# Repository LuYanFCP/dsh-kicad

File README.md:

# dsh-kicad

English | [中文](README.zh.md)

KiCad for [DeepSeek Harness](https://github.com/deepseek-ai/deepseek-harness) (dsh): a native dsh plugin bundle that lets the agent read, edit and check KiCad schematics, with KiCad itself (`kicad-cli`) deciding whether the design is correct.

> Developer preview. Built and tested against dsh `0.2.1-rc.2` and KiCad `10.0.7`. dsh's plugin APIs are pre-stable, so every package pins `engines.dsh` to `>=0.2.1-rc.2 <0.3.0-0`.

## What you get

| Surface | What it does |
|---|---|
| **Tools** (`kicad_*`) | `doctor` (is this machine ready: kicad-cli and KiCad 8+, libraries, Python, with fixes and install commands), `read_schematic`, `list_components`, `get_symbol_pins`, `list_nets` (KiCad netlist), `search_symbols` (installed libraries), `erc`, `drc`, `render` (SVG, PNG attached as an image for image-capable models; for boards KiCad's 3D view from any side or angle), `export` (netlist/BOM), `simulate` (SPICE verification with ngspice: operating point, transient and AC runs, with requirement assertions judged on the numbers, see [Simulation](#simulation)), `sim_model` (find the SPICE models in a model file or folder, with their pins), `check_mcu` (static check of how a microcontroller is wired, see [MCU wiring check](#mcu-wiring-check)), `datasheet` (read a part's datasheet PDF: its sections, search, whole pages) and `check_design` (unit tests for the schematic, quoted from the datasheets; see [Datasheet checks](#datasheet-checks)), `simulate_firmware` (run an ATtiny or ESP32 firmware against the board, see [Firmware against the board](#firmware-against-the-board)), `export_fab` (Gerber/drill/position/BOM zip with 3D previews, refused until KiCad finds the board ready, see [Fab output](#fab-output)), `fab_preset` (JLCPCB/PCBWay design rules), `create_schematic`, and `edit_schematic` — an atomic batch of edits (add/move/remove symbols, set values/footprints/properties, wires, labels, power symbols, junctions, no-connects, pin-to-pin wires routed around parts and other nets, pin-to-net connections, plus layout by function: titled block frames, moving a part or a whole block together with its wiring, page size and title block); for boards `read_pcb` (outline, layers, rules and net classes, footprints with courtyards and pad nets, zones, DRC's unrouted count) and `edit_pcb` — an atomic batch (board outline and mounting holes, moving, flipping and locking footprints, design rules and net classes in the `.kicad_pro`, tracks with pad-to-pad endpoints, vias, zones, keepouts, silkscreen text and reference designators, removal by uuid); and `update_pcb` — Update PCB from Schematic, headless: a new board gets KiCad's empty board, a default stackup and a placeholder outline; on an existing board placed footprints stay put, new ones are staged beside the outline, and nets, values and fields follow the schematic; it refuses with the `REF:PIN`s to fix, and KiCad's schematic parity check judges the result; and `autoroute` — routes the board with [Freerouting](https://github.com/freerouting/freerouting), keeping hand-routed (locked) and existing tracks, refilling copper pours, with KiCad's DRC as the verdict (see [Routing](#routing)). Untouched file text stays byte-identical. |
| **Policy** | Design edits go through dsh approval (`ask`); writes are confined to the session's working directory (a monotonic guard); after every successful edit KiCad ERC (schematic) or DRC (board edit or fab preset, zones refilled; with the schematic parity count after `update_pcb`) runs and its verdict is appended to the tool result, and so are the project's design checks that fail after a schematic edit; the system prompt gets stable KiCad working rules and a dynamic "KiCad project in this directory + last ERC/DRC" context. |
| **Skills** | `kicad-agent-workflow`, `kicad-design-brief`, `kicad-erc-triage`, `kicad-drc-triage`, `kicad-schematic-design`, `kicad-datasheet-checks` (read each part's datasheet and keep its requirements as checks), `kicad-pcb-layout` (from the synced schematic to the fab files: rules, placement, critical nets, GND pour, autoroute, DRC, fab output, each step judged by KiCad), `kicad-simulate`, `kicad-mcu-check`. |
| **Commands** | `/erc`, `/drc`, `/bom`, `/simulate`, `/design-checks`, `/mcu-check` and `/mcu-sim` (model-free, run on the project's root design), `/kicad-fab` (fab zip), `/kicad-render`, `/kicad-doctor` (environment check), `/kicad-install` (install KiCad, the Freerouting autorouter or Espressif's QEMU for ESP32 firmware simulation, see below). |
| **Agent preset** | `eda` — a standard-like tool set with an electronics-design persona. The KiCad tools are global, so every preset can use them. |
| **Web UI** | Right-sidebar viewer for `*.kicad_sch` / `*.kicad_pcb` with two modes: **Interactive** — the embedded [KiCanvas](https://github.com/theacodes/kicanvas) viewer (hierarchical sheets, symbol/footprint/net inspection, layer toggles, KiCad or Witch Hazel theme, reloads when the file changes) — and **SVG** (kicad-cli render, pan/zoom, multi-sheet, Render button, re-renders a board by itself when it changes; also the automatic fallback); boards also get **3D**, modelled on KiCad's 3D Viewer (see [3D view](#3d-view)); conversation cards for ERC/DRC, schematic and board edits (with the automatic ERC/DRC verdict), Update PCB (the changes, the parts waiting for placement, KiCad's parity count), autoroute (what Freerouting added, KiCad's unrouted count and DRC errors), fab output (the gate, the files, **Download zip**, the 3D preview) and the environment check; with **Follow agent** on, a board opens in the sidebar while the agent syncs, edits or routes it, as a schematic does; settings pages for the sidecar (the kicad-cli, Python, Java, Freerouting, ngspice and QEMU paths, plus the KiCad environment check and **Install KiCad**) and the policy (approval, auto-ERC, auto-DRC, auto-render). The viewer and failed tool cards show a notice with **Install KiCad** when KiCad is missing or too old. |
| **Standalone MCP server** | The Python sidecar speaks MCP over stdio, so Claude Code or an RL environment can use the same tools without dsh. |
| **KiCad side (optional)** | An IPC plugin with an "Open in DSH" toolbar action. |

## Architecture

```
dsh-kicad-bundle  (cordis.patch.yml: global rows + presets/eda.patch.yml)
├─ dsh-kicad-bridge     Host  ctx.kicad service; runs the Python sidecar through ctx.subprocess, speaks MCP to it
│    └─ sidecar/        Python ≥3.10, stdlib-only core: lossless .kicad_sch S-expression editing, symbol libraries,
│                       pin geometry, kicad-cli (ERC/DRC/netlist/BOM/SVG), fab output; optional extras: png (cairosvg), ipc (kicad-python)
├─ dsh-tool-kicad       Host  kicad_* tools (defineTool), paths resolved against the session working directory
├─ dsh-kicad-policy     Host  tools.guard + tools/pre-execute (ask/deny) + tools/post-execute (auto ERC/DRC) + prompt section/context
├─ dsh-kicad-skills     Host  skill provider + /erc /drc /bom /kicad-fab /kicad-render
└─ dsh-client-ui-kicad  Client sidebarRightTabs type + tool.call.toolview rows + plugins.row.config pages
kicad-plugin/           KiCad IPC plugin ("Open in DSH")
market/                 plugin-market index example
```

Design decisions:

- **Files first, headless.** Schematics are edited as files (`.kicad_sch` S-expressions) and judged with `kicad-cli`; no KiCad GUI is needed. The IPC API (`kipy`) is only an optional live channel (`ipc_status`), because it needs a running GUI and admits one client at a time.
- **Python sidecar**, not Node → IPC: KiCad's IPC is NNG + protobuf with an official binding only for Python.
- **KiCad decides.** ERC/DRC verdicts come from `kicad-cli`, never from the model.
- **Narrow dsh coupling.** Each package touches dsh only through one adapter module (`src/dsh.ts`, `src/client/dsh.ts`); the Client uses public seams only (`sidebarRightTabs`, keyed slots, `remote.workspaceFiles`, `remote.commands`, config forms) and imports no dsh Client package, as dsh asks of third-party UI plugins.

## Requirements

- dsh `>=0.2.1-rc.2 <0.3` (`npm i -g @deepseek-ai/dsh`), Node `>=22.19`, pnpm 11 (for building from source)
- Python `>=3.10` on `PATH` (`python3`; `python` on Windows) — no Python packages needed for the core
- KiCad 8+ with `kicad-cli` (tested with 10.0.7). Found via the setting, `$KICAD_CLI`, `PATH`, macOS/Windows install dirs, or Flatpak `org.kicad.KiCad`
- Optional: `rsvg-convert`, ImageMagick or the `png` extra for PNG renders; the `ipc` extra for the IPC channel; [ngspice](https://ngspice.sourceforge.io/) (`ngspice` on `PATH`, or `$NGSPICE`) for `kicad_simulate`; `pdftotext` from poppler (`poppler-utils`; or `$PDFTOTEXT`) for `kicad_datasheet`

### Check your setup and install KiCad

**Plugins → KiCad → KiCad bridge** shows the environment check: each item (kicad-cli, KiCad version ≥ 8, symbol and footprint libraries, Python ≥ 3.10, optional KiCad 3D models, PNG rasterizer and kicad-python) with its status and how to fix it. `/kicad-doctor` prints the same in a conversation, and the model has `kicad_doctor`; a tool that fails because KiCad is missing names the install command.

When KiCad is missing or too old, the page (and the viewer's notice) lists the ways to install it on this machine:

| Platform | Option | Runs from dsh? |
|---|---|---|
| Fedora | `sudo dnf install -y kicad` | no: needs root, shown with **Copy command** |
| Ubuntu and derivatives | KiCad PPA: `sudo add-apt-repository -y ppa:kicad/kicad-10.0-releases && sudo apt-get update && sudo apt-get install -y kicad` | no (root) |
| Debian | `sudo apt-get install -y kicad` | no (root) |
| Arch | `sudo pacman -S --needed kicad kicad-library` | no (root) |
| openSUSE | `sudo zypper install kicad` | no (root) |
| any Linux with flatpak | `flatpak remote-add --user … flathub` + `flatpak install --user flathub org.kicad.KiCad` | yes, per user, no root (about 1.5 GB) |
| macOS | `brew install --cask kicad` | yes, if Homebrew is installed |
| Windows | `winget install --id KiCad.KiCad -e` | yes, if winget is available (Windows may ask for permission) |
| everywhere | installer from kicad.org | link |

Nothing runs until you click **Install…** and confirm the exact command. dsh never runs `sudo`: root-only options are shown for you to run in a terminal, then **Check again**. A running install shows its log and can be stopped; when it finishes the bridge restarts its sidecar and checks again, so the new kicad-cli (including the Flatpak one, via `flatpak run --command=kicad-cli org.kicad.KiCad`) is used without restarting dsh. From a conversation: `/kicad-install` lists the options, `/kicad-install flatpak --yes` runs one, `/kicad-install status` follows it.

The settings page has no session of its own: it runs these checks through your most recent session, so open or start one first.

## Install

### From source (works today)

```sh
git clone https://github.com/LuYanFCP/dsh-kicad && cd dsh-kicad
pnpm install && pnpm run build
dsh plugin --profile web add "$PWD/packages/kicad-bundle"
dsh web
```

`dsh plugin … add <dir>` links the directory; leaf packages resolve through this checkout's `node_modules`, and dsh maps `@deepseek-ai/*` imports to the running installation. Rebuild and restart dsh after code changes. In the Web UI you can also use **Plugins → Install** with the same absolute path.

### Paste the repository URL (simplest)

In dsh, **Plugins → Add plugin**, enter `https://github.com/LuYanFCP/dsh-kicad` and install (or `dsh plugin --profile web add https://github.com/LuYanFCP/dsh-kicad`). The repository root is itself the `dsh-kicad` bundle; it loads the prebuilt `dist/dsh-kicad`. Append `#<tag-or-commit>` to pin a version.

### From the plugin market (search inside dsh)

dsh finds plugins through **plugin markets**: JSON indexes you add once. This repository publishes one.

1. **Plugins → Experimental plugins → More → Custom plugin markets**: switch it on. A **Discover** tab appears.
2. **Discover → Add index source**: `https://raw.githubusercontent.com/LuYanFCP/dsh-kicad/main/market/index.json`
3. Search, e.g. `kicad`, `原理图`, `电路板`, `circuit board`, then **Install → Enable now**. No restart needed.

The market entry installs `dist/dsh-kicad`, a single self-contained package built by `pnpm run dist` (`scripts/pack-dist.mjs`), from a pinned Git commit. The same package installs directly:

```sh
dsh plugin --profile web add "git+https://github.com/LuYanFCP/dsh-kicad.git#<commit>&path:/dist/dsh-kicad"
```

To publish a new version: `pnpm run dist`, commit, then add a version to `market/index.json` with that commit and check it with `node market/validate.mjs <dsh>/node_modules/@deepseek-ai/dsh-plugin-market-index`.

## Use

1. Open a session whose workspace contains a KiCad project (sidebar **Add workspace**). Optionally pick the **EDA agent** preset.
2. Ask, e.g. *"Add a 100 nF decoupling capacitor between +3V3 and GND next to U1 and make ERC pass."* The agent reads the design, sends one `kicad_edit_schematic` batch (you approve it), and reads the ERC verdict that the policy appends.
3. Open the `.kicad_sch` from **Workspace files**: the KiCad tab shows the render, refreshed after each agent edit; **Render** re-renders on demand.
4. `/erc`, `/drc`, `/bom` work without the model.
5. **Plugins → KiCad → KiCad bridge / KiCad policy** hold the settings.

### Schematics by functional block

A new design is drawn block by block, like a reference design. The agent first plans the blocks (title, parts, area on the page). It then builds one block per `kicad_edit_schematic` call and frames it with `add_block`: a dashed frame titled with the block's job and main part (`3V3 LDO — AMS1117-3.3`, `MCU — ATtiny85`), with short notes inside where a choice needs explaining. Blocks connect only through net labels and power symbols. After every batch that places or moves parts, the edit result names the parts outside every block, and the agent is not done while there are any. `kicad_read_schematic` lists the same parts as `outside_blocks`. An existing schematic keeps its organisation unless you ask to reorganise it. The board placement below follows the same blocks.

### Datasheet checks

A part's limits and the parts it needs come from its datasheet, not from the model's memory. `kicad_datasheet {path, reference | lib_id | url | pdf, query?, pages?}` reads the datasheet: the symbol's own link, a URL the agent found with `web_search`, or a PDF in the workspace. It downloads the PDF once into `.dsh-kicad/datasheets/`, extracts the text per page with `pdftotext`, and returns the pages of the usual sections (absolute maximum ratings, operating conditions, electrical characteristics, application information, layout), the lines matching a query, or whole pages. A link that leads to a web page or a zip is refused with what to do instead.

`kicad_check_design` turns those pages into unit tests for the schematic. Each check states one requirement and quotes the words it comes from. The checks are kept in `design-checks.json` next to the schematic, and the tool judges them on KiCad's netlist and the part values. Rules:

- `max_voltage`, `voltage_range`;
- `voltage_difference` (a regulator's dropout headroom);
- `capacitance` (every capacitor between two nets);
- `resistance` (pull-ups, pull-downs, series resistors);
- `same_net`;
- `led_current` (rail voltages, Vf and the series resistor).

A check counts only when its source holds: the quote must be in the datasheet text (or in a workspace file such as `design-brief.md`, for the user's own numbers), and it must state the check's numbers. Otherwise the check is CANNOT VERIFY, never passed. After every schematic edit the checks re-run and the failing ones are appended to the result; `/design-checks` runs them without the model.

On the AMS1117-3.3 the datasheet says "The addition of 22µF solid tantalum on the output will ensure stability for all operating conditions". A design with the usual 10 µF fails that check (`capacitance +3V3 → GND = 10.1 µF < 22 µF`); with 22 µF it passes. The `kicad-datasheet-checks` skill says what to take from each kind of part.

### Board placement

After `kicad_update_pcb` creates a board, one `kicad_edit_pcb` operation, `auto_place`, lays it out from the schematic's functional blocks (the `add_block` frames; without them its sheets, else net connectivity): each block stays together, connectors sit on the board edge facing out (a footprint's "PCB Edge" mark lands on the edge), decoupling capacitors go next to their IC's power pins and crystals next to their IC, power parts get extra room, and the outline is sized to fit (a drawn outline is kept and filled instead). `place_block` lays out one block in a given spot or rectangle. `kicad_read_pcb` then reports courtyard overlaps, footprints outside the outline and the total ratsnest length, and `kicad_render` with `view: "3d"` shows the result. On the usb-attiny85 board it gives no courtyard overlap, everything inside the outline, the USB-C on the edge, and a ratsnest of 214 mm against 345 mm for random placement ([details](docs/pcb-architecture.md#placement-12)).

### Routing

`kicad_autoroute {pcb, nets?, exclude_nets?, passes?, timeout?}` writes the board as a Specctra design, runs Freerouting headless, and adds only the new tracks and vias; footprints never move. Every track and via already on the board is fixed wiring, so the agent routes critical nets by hand first (power, USB or differential pairs, a crystal: `kicad_edit_pcb` `add_track` / `add_via` with `locked: true`) and the router completes the rest. Copper zones (a GND pour on both layers) are refilled and saved afterwards by `kicad-cli pcb drc --refill-zones --save-board`, whose verdict (unrouted count, DRC errors, schematic parity) is the result. The run can be cancelled from dsh and stops at `timeout` (default 300 s), keeping what it routed; the design, session and log stay in `<project>/.dsh-kicad/autoroute/`. When connections stay open, the result suggests routing them by hand or, on an `auto_place`d board, clearing the routes (`remove_tracks`) and placing again with more room (`gap: 2, group_gap: 4`): that routes the usb-attiny85 example completely.

Freerouting (GPL-3.0) is a separate Java program and is not bundled. `/kicad-doctor` checks for Java and Freerouting; `/kicad-install freerouting --yes` downloads the pinned release jar (2.5.0, about 65 MB, SHA-256 checked) into your data directory (`~/.local/share/dsh-kicad/freerouting` on Linux), never with `sudo`. Freerouting 2.5.0 needs **Java 25+**: the doctor lists the package-manager command or the [Temurin JRE](https://adoptium.net/temurin/releases/?package=jre). The bridge's `java` and `freerouting` settings point at an existing Java or jar.

### Simulation

`kicad_simulate {path, analyses?, assertions?, probes?, timeout?}` checks what a schematic *does*, not only how it is wired. KiCad exports the SPICE netlist (`kicad-cli sch export netlist --format spice`, which reads the symbols' `Sim.*` properties, so a design simulated here also simulates in KiCad's own Simulator), ngspice runs it headless, and each requirement is an assertion the tool judges on the numbers, as ERC and DRC are judged by KiCad: the model never decides.

- Analyses: `op` (DC operating point, the default), `tran {stop, step?}`, `ac {start, stop, points?}`; one of each per call.
- Probes: `V(net)`, `V(a,b)`, `I(R1|C1|L1|D1|V1)`. Assertions: `{probe, min?, max?, equals? + tol | tol_pct, abs?, measure?, at?, from?, to?, ref?}` with SPICE-style numbers (`10k`, `100n`, `3.3`, `20m`). Measures: `final`, `initial`, `max`, `min`, `mean`, `rms`, `pp`, `at` (transient); `gain_db`, `phase_deg`, `peak_gain_db`, `lowpass_cutoff_hz`, `highpass_cutoff_hz` (AC, `ref` for gain relative to the input).
- Example: a 3.3 V rail `{probe: "V(3V3)", min: 3.2, max: 3.4}`, an LED `{probe: "I(D1)", min: "5m", max: "15m", abs: true}`, a low-pass `{probe: "V(OUT)", analysis: "ac", measure: "lowpass_cutoff_hz", equals: 1000, tol_pct: 5}`.
- The circuit needs a ground net, sources from `Simulation_SPICE` (`VDC`, `VSIN`, `VPULSE`, `IDC`) and a model for every part that matters: R, C and L simulate from their value; a diode or LED needs `set_sim_model {reference, device: "D", params}` (hidden `Sim.Device`) (the tool refuses otherwise, because without it KiCad wires the diode backwards); ICs, regulators and transistors need a vendor model (below). Parts without a model are left out and listed in the result.
- **Vendor models.** `kicad_sim_model {path, name?}` lists the `.subckt` (with their pins and the comment above them) and `.model` definitions in a model file, or in every model file below a folder. `kicad_edit_schematic` `set_sim_model {reference, library, name, pins?}` binds one to a symbol: it writes the hidden `Sim.Library` (relative to the project), `Sim.Name`, `Sim.Device` and `Sim.Pins`, matches symbol pins to model pins by name, and refuses with both pin lists when it cannot (give `pins: {"1": "GND", "2": "OUT", "3": "IN"}`), because KiCad trusts a wrong `Sim.Pins` and simulates the wrong circuit. `{reference, device: "D", params}` sets a built-in device without a file. Models come from files you provide; none are bundled, and the agent is told not to invent any. Subcircuit internals stay out of the result.
- **Tolerances.** `monte_carlo: {runs?, seed?, tolerances?, distribution?, min_pass_rate?}` repeats the run with R, C and L values (defaults ±5 %, ±10 %, ±10 %; `tolerances: {R: 1, C1: "20%", V1: 2}` in percent by part letter or reference, V and I sources by DC level) drawn at random, uniform within the tolerance or gaussian with 3σ at the tolerance, and reports per assertion how many runs held, the min, mean, max and the first failing draw. Seeded, so repeatable; `min_pass_rate` (default every run) accepts a share below 100 %. Only plain R, C, L values and source levels vary, not the parameters inside vendor models.
- **Requirements stay with the project.** `save_spec: true` writes the analyses, assertions and `monte_carlo` of a call to `<schematic name>.sim.json` (plain JSON: `analyses`, `assertions`, `probes`, `monte_carlo`, `timeout`; `spec` names another file). Later `kicad_simulate` calls and `/simulate` use that file when it exists, so a change is re-verified against every saved requirement without retyping them; arguments named in a call replace the same key of the file.
- ngspice is a separate install: `/kicad-doctor` checks for it and lists the command for this machine (`sudo dnf install ngspice`, `sudo apt-get install ngspice`, `brew install ngspice`, ...). The netlist, deck, rawfiles and log are kept in `<project>/.dsh-kicad/sim/<name>/`. `/simulate` runs the project's saved requirements (an operating point when there are none) without the model; the `kicad-simulate` skill teaches the agent to turn requirements into assertions and iterate.
- What it cannot say: anything about firmware or a part without a SPICE model, signal integrity, EMC or heat.

### MCU wiring check

`kicad_check_mcu {path, reference?, requirements?}` checks how each microcontroller is wired, from KiCad's netlist and a per-family pin table (an MCU *provider*), and judges the result itself. It is a static check, not a firmware simulation: it cannot know what the firmware does with a pin.

- **Findings** (error / warning / info, each with the pin, the net and a fix). For the classic ESP32: a strapping pin held at the wrong level at reset (GPIO0 tied to ground, GPIO12 high or strongly pulled up, which selects 1.8 V flash and stops the chip booting, GPIO2 pulled up), reserved flash or PSRAM pins in use (GPIO6-11, and 16/17 on PICO, WROVER and the -R2 modules), an input-only GPIO (34-39) that nothing can drive or that floats behind a button, an unconnected or unpulled EN, less than 10 µF on the supply. For the ATtiny85: RESET unconnected or relying on the weak internal pull-up, less than 100 nF on VCC; its peripherals sit on fixed pins, so requirements like `i2c_sda`, `i2c_scl`, `spi_*`, `pwm`, `adc` are judged against them (an I²C SDA on PB4 fails). For the ATmega48/88/168/328 (the Arduino UNO/Nano chip; pins named by port, PB0-PD7): RESET unpulled, VCC and AVCC decoupling, AVCC that does not reach VCC (the datasheet wants it connected even without the ADC; an LC filter counts), AREF tied straight to a rail (selecting the AVCC or 1.1 V reference would short it) or without its capacitor, a crystal on XTAL1/XTAL2 without load capacitors, PB6/PB7 used as GPIOs (only with the internal oscillator), ADC6/ADC7 (analog only, no pull-up) behind a button; requirements `pwm` (OC0A/B, OC1A/B, OC2A/B), `adc`, `i2c_*` (PC4/PC5), `spi_*`, `uart_tx`/`uart_rx` (PD1/PD0), `int0`/`int1`. For the **Arduino Nano and UNO** module symbols (pins D0-D13, A0-A7): D0/D1 in use (the board's USB serial), D13 as an input on a Nano (its LED pulls it to about 1.7 V), A6/A7 analog only, AREF tied to a rail, and the same requirements by Arduino pin.
- **Requirements** say what the firmware needs from the board: `[{net: "VBAT_SENSE", needs: "adc1"}, {pin: "U1:IO25", needs: ["output", "dac"]}]`; `needs` is `output` (not input-only), `input`, `adc` / `adc1` (usable with WiFi) / `adc2`, `dac`, `touch` or `boot_free` (not a strapping pin). Each is judged against the GPIO the signal is on; the agent is told to choose GPIOs for them before wiring.
- **Cannot verify, never passing.** An MCU no provider covers (ESP32-S3, STM32, other ATtiny and ATmega parts, the Nano Every, a custom symbol whose pins the table cannot read, ...) is reported as `cannot_verify` with the reason; the verdict is then neither passed nor failed, and the requirements on it are `?`.
- **Providers are data.** `mcu_data/esp32.json` (classic ESP32 modules and PICO), `attiny85.json` (the 8-pin ATtiny25/45/85), `atmega328p.json` (the ATmega48/88/168/328 family), `arduino_nano.json` and `arduino_uno.json` (the tables were transcribed from the vendors' datasheets, Espressif's hardware design guidelines and Arduino's schematics, so check them against your part's datasheet) says which symbols it covers and, per GPIO, what matters. A project adds its own family as `<family>.mcu.json` next to the schematic (`id`, `name`, `match`, `gpio_pin_pattern` with `ports` for pins named by port, `pin_aliases`, `gpios`; same structure, same rules); the project's file wins for the same `id`. `/mcu-check` runs the check on the project schematic without the model; the `kicad-mcu-check` skill teaches the agent to set requirements first and fix the findings.

### Firmware against the board

`kicad_simulate_firmware {path, firmware?, stimuli?, assertions?, duration?, clock_hz?, ...}` runs a firmware image on a simulated **ATtiny25/45/85** or **classic ESP32** wired as the schematic says and judges what the board does, so "pressing the button lights the LED within 20 ms" is checked rather than assumed. The firmware is one you built: for the ATtiny a `.hex` or `.elf` (avr-gcc, PlatformIO, Arduino; an ELF also carries the initial EEPROM), for the ESP32 a merged flash image (see below); the plugin never builds, writes or invents one.

- **The chip** is a pure-Python AVR simulator (no dependencies) that follows the datasheet (Atmel 2586Q, read in full for this): the ATtiny25/45/85 instruction set and memory sizes; GPIO; the external, pin-change and every peripheral interrupt in vector order; **Timer0 and Timer1** (normal, CTC, phase-correct and fast PWM, toggle outputs; compare values latched at TOP/BOTTOM as the hardware does; Timer1 with the 64 MHz PLL clock, OCR1C as TOP and the complementary outputs); the **ADC** (single-ended and differential channels with gain, unipolar and bipolar, the bandgap, the temperature sensor, Vcc / 1.1 V / 2.56 V / AREF references, free running, the 13/25-clock conversion time); the **analog comparator**; **EEPROM** (3.4 ms writes, erase-only and write-only modes, persisting across resets, loaded from an ELF's `.eeprom`); the **watchdog** (reset and interrupt mode, the timed-sequence rules, wake-up from power-down); **resets** (the RESET pin, the watchdog, the 64 ms start-up delay, MCUSR flags); the **USI in three-wire mode** (SPI as master or slave, software strobe or external clock); idle and power-down sleep. It is checked against programs compiled by avr-gcc at four optimisation levels (148 result bytes of arithmetic, sorting, CRC, soft-float compared with Python) and against known timings.
- **The board** is a DC network: resistors, switches, the pin drivers (40 Ω) and internal pull-ups (35 kΩ), the RESET pin's own pull-up (45 kΩ), rails and ground. A button the scenario presses closes its switch (a switch from the RESET net to ground resets the chip); the chip reads whatever the network makes of the pin; an LED reports whether it would light (1.8 V forward); a PWM pin is high for its duty cycle and the network is solved for each combination. Transistors, ICs and other parts on those nets are treated as open circuits and listed in the result.
- **Scenarios.** `stimuli`: `{at: "30ms", press: "SW1", name: "press"}`, `release`, `toggle`, `{at, drive: "NET", level: high|low|release|<volts>}` (an ideal source that also overrides a rail, e.g. a battery that sags), `{at, temperature: 85}`. `assertions`: a subject (`{led: "D2", is: "on"}`, `{pin: "PB4", level: "high"}`, `{net, level}`, `{net, min, max}` in volts, `{pin, duty, tol}` / `{pin, freq, tol_pct}` for a PWM pin, `{led, min, max}` for the fraction of time an LED is lit) and a moment (`at`, `{after: "press", within: "20ms"}`, `{from, to}` throughout), or logged events: `{reset: "watchdog", after, within}`, `{resets: 0, at}`, `{eeprom: 0, is: 42, at}`, `{usi: "tx", nth: 1, is: 165, by}`. Other inputs: `eeprom` (initial bytes), `usi_input` (what a slave shifts in), `startup_ms`, `rstdisbl` (PB5 as a GPIO), `vcc`, `led_vf`.
- **Keep it with the project.** `save_scenario: true` writes the arguments to `<schematic name>.fw.json`; later calls and `/mcu-sim` use that file when it exists, so every saved requirement is re-checked after a change (arguments named in a call replace the same key of the file).
- **Hazards, unasked.** A floating input the firmware reads (a button without a pull-up), an output fighting a switch (overcurrent: a driver into a closed switch to ground is 125 mA), an input stuck between the logic levels, and every reset.
- **What it will not pretend.** The USI in two-wire mode (I²C), the dead-time generators, forced output compares, a Timer0-clocked USI, Timer0 mode 5 and brown-out are not simulated. A firmware that uses one stops the run with the reason and the time; assertions about later times are `cannot verify`, never passed, and so is the verdict. Other MCUs (STM32, ESP32-S2/S3/C3, other AVRs) are refused; `kicad_check_mcu` still checks their wiring.
- Speed: a sleeping chip costs nothing; a busy loop runs at a few million instructions per second, with a wall-clock `timeout`. `clock_hz` defaults to 1 MHz (the factory 8 MHz RC with the divide-by-8 fuse): set it to the clock the firmware was built for.

**The classic ESP32** (WROOM/WROVER modules and PICO) runs on [Espressif's QEMU](https://github.com/espressif/qemu) (`qemu-system-xtensa -machine esp32`): the ROM, the second-stage bootloader, your application and FreeRTOS on both cores, so an ESP-IDF or Arduino-ESP32 build runs as it is. QEMU is a separate install: `kicad_doctor` reports it, `/kicad-install qemu-esp32` downloads Espressif's release (checked against its SHA-256, no root), and the one ESP-IDF installs (`idf_tools.py install qemu-xtensa`) is found too; the `qemu` setting or `$QEMU_XTENSA` points to another.

- **Firmware**: the merged flash image (bootloader at 0x1000, partition table, application: ESP-IDF's `esptool.py --chip esp32 merge_bin -o flash.bin @flash_args` in the build folder, or Arduino's `.merged.bin`), or the build folder's `flasher_args.json`, which is merged for you. It is padded to a flash size QEMU accepts; the file itself is never written.
- **The pins.** QEMU's ESP32 GPIO peripheral is a stub and IO_MUX and RTC_IO are not modelled, so the sidecar watches the chip through QEMU's gdb stub and does every load and store of those registers itself: outputs, open drain, the internal pull-ups and pull-downs, input enables and the GPIO matrix follow the firmware, a read-modify-write (ESP-IDF's way of setting a pad up) starts from what the chip holds, and a load of `GPIO_IN` gets the levels the board gives the pins. Pins are `GPIO2`, `IO2` or `U1:IO2` in assertions. The board side is the same DC network (pin drivers by drive strength, about 33 Ω at the default; 45 kΩ pulls; ESP32 thresholds).
- **Boot and reset.** The strapping pins (GPIO0, 2, 4, 5, 12, 15) are solved at power-on and handed to QEMU: holding GPIO0 low really starts the serial bootloader, GPIO12 high is an error (1.8 V flash). EN low holds the chip in reset until it rises; resets are logged with their cause (`{reset: "watchdog"}`, also `power-on`, `software`, `external`, `deep-sleep`, `brownout`). The UART0 output is captured: `{uart: "ready", by: "2s"}` or `{uart: "Guru Meditation", is: "absent"}`.
- **GPIO interrupts.** QEMU's GPIO stub raises none, so the sidecar keeps the interrupt status itself: an edge or level the board gives a pin latches it as the pin's `GPIO_PINn` says (rising, falling, any edge, low or high level), `PCPU_INT`/`ACPU_INT` show it per CPU, and the GPIO source of QEMU's interrupt matrix is raised through QEMU's qtest socket. The CPU takes the interrupt the firmware mapped, so `attachInterrupt`, `gpio_isr_handler_add` and MicroPython's `Pin.irq` run their handlers, about 2 ms after the stimulus (the time the simulator needs to stop next to it). The result lists every interrupt.
- **PWM (LEDC).** QEMU keeps few of the LED PWM controller's registers (no duty readback, no fades, no interrupts), so the sidecar keeps it too: a pad the GPIO matrix routes to a channel carries the PWM wave its registers give (the timer's clock and fractional divider, the resolution, `HPOINT`, the dithering bits, `IDLE_LV` when the output is off), including hardware fades and their end interrupt. `{pin, duty}`, `{pin, freq}` and LED brightness (`{led, min, max}`) then work as on the ATtiny: MicroPython's `PWM(Pin(2), freq=1000, duty_u16=16384)` reports 998 Hz, and so does the simulation. A fade shows in the timeline by its first and last step. A timer that is paused or held in reset while it drives a board pad, and the timers' overflow interrupts (one every period), stop the run.
- **ADC.** QEMU does not model the SENS block the two SAR ADCs sit in, so the sidecar keeps it too: a one-shot conversion through the RTC controller (what ESP-IDF's `adc_oneshot_read`, Arduino's `analogRead` and MicroPython's `ADC` do) reads the voltage the board puts on the channel's pad (a divider, a net you `drive`), with the channel's attenuation and bit width. The reading is a typical chip's: the inverse of ESP-IDF's own calibration (its line fitting, and its lookup table at the top of the 12 dB range) for the 1100 mV reference the simulated chip carries in eFuse. `analogReadMilliVolts`, `adc_cali_raw_to_voltage` and MicroPython's `read_uv()` therefore give the board's voltage back to within a millivolt: MicroPython's `ADC(Pin(34), atten=ADC.ATTN_11DB)` on a 1.65 V divider reads 1872 and reports 1650 mV. The result lists each channel's first conversion and every change (the pad's voltage, the reading, its calibrated value). Noise, the spread between chips and ADC2's arbitration with WiFi are not simulated. A pad that floats reads 0 and is a hazard; a PWM wave on the pad reads as its average only through an RC filter (a capacitor on the net), otherwise the run stops, as it does for the hall sensor.
- **Time** is QEMU's virtual clock (`-icount`): every instruction advances it by 8 ns, so busy code takes the same simulated time on any host, while idle time (the CPU waiting in WAITI, as the FreeRTOS idle task does) passes in real time. A run therefore takes at least its simulated duration of wall-clock time. Timings inside the application repeat to well under a millisecond from run to run; the boot of a dual-core firmware varies by some tens of milliseconds (QEMU runs the two cores in turns). The simulated time includes the boot: about 0.2 s for a small program, about 2 s for MicroPython, so put stimuli after the firmware has set its pins up (the timeline shows when). A firmware that sleeps with no timer pending (FreeRTOS's tick always is) stops QEMU's clock: the time until the next stimulus then passes for the board only (the result says so), and with no stimulus left the run ends there as a stall. `duration` defaults to 2 s (at most 30 s).
- **What it will not pretend.** A pad on the board driven by another peripheral (I2C, SPI, RMT) has a level this simulator does not know, so the run stops there; so does a crash (`Guru Meditation`, `abort()`) and a firmware waiting for hardware that never answers. Assertions after that point are `cannot verify`. Hardware the simulation does not emulate (WiFi, Bluetooth, the touch pads, the temperature sensor, ...) that the firmware touched while it ran is listed under `not_emulated`.

### 3D view

Open a `.kicad_pcb` and pick **3D** next to Interactive / SVG, much like KiCad's View → 3D Viewer. The Host exports the board as a binary glTF scene (`kicad-cli pcb export glb` with copper, pads, zones, mask, silkscreen and the footprints' 3D models) into `<project>/.dsh-kicad/render/<board>/`, cached by board content, so reopening is instant. The view reads it through `remote.workspaceFiles` (raw bytes; 2 MiB windows beyond dsh's 32 MiB whole-file limit) and shows it with three.js: drag to rotate, right- or Shift-drag to pan, scroll to zoom; **Top / Bottom / Front / Back / Left / Right / Iso**, **Perspective / Orthographic**, **Components** and **Reset view**. When the board changes (an agent edit, KiCad saving) it is exported again after a quiet second and the camera stays where it was; a failed export keeps the last good model and says why.

**KiCad render** renders the current camera with KiCad's own renderer (`kicad-cli pcb render --quality high`, a few seconds), mapping the orbit camera to `--rotate` / `--zoom` / `--pivot` / `--perspective`, for KiCad's exact look. Without WebGL the 3D mode shows such renders, with the same view buttons.

three.js (about 645 KB, 163 KB gzipped) is a separate client chunk, `lib/client.three.js`, that dsh loads the first time a board opens in 3D; the main client module grew by about 28 KB.

The model gets the same angles: `kicad_render {view: "3d", side?, rotate?: "-45,0,45", zoom?, pivot?, perspective?, quality?: "basic" | "high"}` (the defaults and results are unchanged; `/kicad-render <board> --3d --rotate=-45,0,45` does it from a conversation).

**KiCad's 3D model library.** Component bodies come from KiCad's 3D models (`${KICAD10_3DMODEL_DIR}`), which most Linux distributions package separately. `/kicad-doctor` checks for them (the variable is resolved like KiCad: environment, then Preferences → Configure Paths, then the built-in default), and the 3D view shows a notice with the fix when footprints reference models that cannot be found:

| Platform | 3D models | Runs from dsh? |
|---|---|---|
| Fedora | `sudo dnf install -y kicad-packages3d` | no: needs root, shown with **Copy command** |
| Debian, Ubuntu (incl. the KiCad PPA) | `sudo apt-get install -y kicad-packages3d` | no (root) |
| Arch | `sudo pacman -S --needed kicad-library-3d` | no (root) |
| openSUSE | `sudo zypper install kicad-packages3D` | no (root) |
| Flatpak KiCad | `flatpak install --user flathub org.kicad.KiCad.Library.Packages3D//stable` | yes, per user (about 640 MB download) |
| macOS | included in KiCad.app (DMG and Homebrew cask); `brew reinstall --cask kicad` restores them | yes, with Homebrew |
| Windows | included in the full installer (and `winget install KiCad.KiCad`); keep the "3D models" component | link |
| everywhere | the [kicad-packages3D](https://gitlab.com/kicad/libraries/kicad-packages3D/-/tags) archive for your KiCad version, then set `KICAD10_3DMODEL_DIR` | link |

The distribution packages are about 270 MB to download and 3.1 GB installed. Without them the 3D view and renders show the bare board with pads, copper and silkscreen.

### Fab output

`/kicad-fab [board.kicad_pcb] [--preset jlcpcb|pcbway] [--force] [--step] [--ipc2581] [--odb]` (the agent's `kicad_export_fab`) lets KiCad judge the board first. DRC errors, unrouted connections, schematic parity issues (when the schematic sits next to the board) and, with a preset, errors against that fab's limits refuse the export, and nothing is written. `--force` exports anyway; the result and `fab-manifest.json` say so.

Output goes to `<project>/fab/<preset or kicad>/`: Gerbers for copper, mask, paste, silkscreen and Edge.Cuts with the Gerber job file; Excellon drill files with a Gerber X2 drill map; `assembly/` with the position CSV and BOM (plus JLC BOM/CPL with `--preset jlcpcb`); `preview/` with front and back 3D PNGs; and `<board>-<preset or fab>.zip` with everything except the previews.

`kicad_fab_preset` makes a fab's limits (minimum track, clearance, drill, annular ring, hole spacing, copper to edge) the project's design rules, so `kicad_drc` checks what the fab can make: board setup minimums go into the `.kicad_pro`, custom rules into a managed block of the `.kicad_dru` (your own rules stay). The values come from each fab's published capabilities ([`presets/`](packages/kicad-bridge/sidecar/src/dsh_kicad_sidecar/presets)); the fab's own review has the last word.

### Standalone MCP server (Claude Code, RL environments)

```sh
claude mcp add kicad -- uvx --from "git+https://github.com/LuYanFCP/dsh-kicad#subdirectory=packages/kicad-bridge/sidecar" dsh-kicad-sidecar --root .
# or from a checkout, without uv:
PYTHONPATH=packages/kicad-bridge/sidecar/src python3 -m dsh_kicad_sidecar --root /path/to/project
```

`--root` (repeatable) confines file access. `--call <tool> --args '<json>'` runs one tool and prints its result.

### KiCad "Open in DSH" (optional)

Copy `kicad-plugin/` into KiCad's IPC plugin directory (KiCad 9/10: the `plugins` folder under your KiCad documents directory, e.g. `~/Documents/KiCad/10.0/plugins/dsh-kicad`), enable **Preferences → Plugins → Enable KiCad API**, and restart KiCad. The toolbar button copies the project path to the clipboard and starts `dsh web` from the project directory (dsh web has no workspace flag, so use **Add workspace** and paste).

## Configuration

| Row (`cordis.patch.yml` id) | Field | Default | |
|---|---|---|---|
| `kicad-bridge` | `launcher` | `python` | `python` runs the sidecar from source; `uv` runs it in a uv venv with `uvExtras` (`png`, `ipc`) |
| | `python` *(live)* | `python3` | interpreter |
| | `kicadCli` *(live)* | auto | kicad-cli path |
| | `java` *(live)* | auto | Java 25+ for Freerouting (`$JAVA_HOME`, then PATH) |
| | `freerouting` *(live)* | auto | `freerouting.jar` (`$FREEROUTING_JAR`, then the jar `/kicad-install freerouting` downloaded) |
| | `ngspice` *(live)* | auto | ngspice for `kicad_simulate` (`$NGSPICE`, then PATH) |
| | `qemu` *(live)* | auto | Espressif's `qemu-system-xtensa` for ESP32 firmware simulation (`$QEMU_XTENSA`, PATH, ESP-IDF's tools, then the one `/kicad-install qemu-esp32` downloaded) |
| | `requestTimeoutMs` | `300000` | |
| `kicad-policy` | `approval` *(live)* | `ask` | `ask` / `allow` for design edits |
| | `autoErc` *(live)* | `true` | ERC after each schematic edit |
| | `autoDrc` *(live)* | `true` | DRC after each board edit (with `--refill-zones` when the board has zones) |
| | `autoRender` *(live)* | `true` | refresh the sidebar SVG after each edit |
| | `restrictToWorkspace`, `extraRoots` | `true`, `[]` | write confinement |
| | `guidance`, `projectContext` | `true` | prompt section / dynamic context |
| `kicad-tools` | `attachRenders` | `true` | attach PNG renders for image-capable models |

*(live)* fields are editable in the Plugins page without restart.

## Develop

```sh
pnpm install && pnpm run build
pnpm test            # vitest: host packages against dsh's real ToolRuntime/SkillRegistry + real sidecar; client in jsdom
pnpm run test:py     # pytest: S-expression round trip (KiCad demo files), schematic and board editing judged by kicad-cli, MCP server
python packages/kicad-bridge/sidecar/tests/make_fixtures.py   # regenerate fixtures with the editor itself
```

Real-dsh smoke test without an API key: install the bundle, then from a directory with a KiCad project run `dsh --profile web --patch scripts/dsh-smoke/smoke.patch.yml --no-open` and read `dsh-kicad-smoke.json`.

The Client is compiled by [`scripts/build-client.mjs`](scripts/build-client.mjs), which reproduces dsh's module-loader artifact (`window.__ModuleLoader__.load({ id, factory(require) })`) with only the shell's platform modules external. [`docs/spike-third-party-bundle.md`](docs/spike-third-party-bundle.md) records how third-party Host + Client loading was verified.

## Known limitations

- Boards are created and kept in sync from the schematic (`kicad_update_pcb`), placed (`auto_place`), edited, routed (`kicad_autoroute`), checked and exported (`kicad_export_fab`). Autorouting needs Java 25+ and Freerouting, which are installed separately (see [Routing](#routing)); dense boards may keep a few unrouted connections for the agent to finish by hand.
- Simulation covers analog behaviour with ngspice; parts without a SPICE model are left out, and firmware, signal integrity, EMC and thermal behaviour are not simulated. Plain Device:LED / Device:D symbols need `Sim.Device` set (see [Simulation](#simulation)).
- Firmware simulation covers the ATtiny25/45/85 and the classic ESP32 (on Espressif's QEMU, a separate install); it refuses what it does not model (see [Firmware against the board](#firmware-against-the-board); on the ESP32 among others deep sleep, pads driven by I2C, SPI or RMT, WiFi and Bluetooth). MCU checks are otherwise static and only cover families with a provider (classic ESP32, the 8-pin ATtiny25/45/85, the ATmega48/88/168/328 and the Arduino Nano/UNO today; the ATmega328P's firmware simulation is in progress); other MCUs are tracked in #31. An ESP32 pin table is only as good as its transcription: verify it against the datasheet of the exact module.
- Fab presets were read from JLCPCB's and PCBWay's capability pages on 2026-10-21 and may drift. The JLC CPL keeps KiCad's rotations; JLCPCB's preview may need per-part rotation fixes.
- Edits cover symbols, properties, wires, labels, power symbols, junctions and no-connects; hierarchical sheet creation, buses and graphic items are not edited.
- New sub-sheet symbols get their instance path from the root sheet one level up; deeper hierarchies may need KiCad's annotation.
- Images reach the model only when the model route declares image input and an attachment store is mounted; otherwise the render tool returns SVG paths.
- Approval needs an interactive approval channel; headless runs without one deny design edits unless `approval: allow`.
- The 3D view needs WebGL (otherwise it shows KiCad renders). Its colours follow KiCad's GLB export, which writes sRGB colours as glTF's linear colour factors; the view reads them as sRGB to match KiCad, so other glTF viewers show the same file lighter.
- The interactive viewer is KiCanvas, vendored at a pinned commit by `scripts/vendor-kicanvas.mjs` (see `packages/client-ui-kicad/vendor/kicanvas/README.md` for the offline/icon/theme patches). It parses KiCad 10 files but ignores tokens it does not know yet; the SVG mode is the kicad-cli ground truth. It needs WebGL2.
- The IPC channel is a status probe plus the KiCad-side launcher; live editing through IPC is not implemented (KiCad's IPC API is PCB-centric).
- The Flatpak path runs kicad-cli as `flatpak run --filesystem=host --filesystem=/tmp --command=kicad-cli org.kicad.KiCad`; this was tested with a stand-in `flatpak`, not a real Flatpak KiCad. The install commands for apt/pacman/zypper/brew/winget are documented but were only exercised on Fedora.
- Checks started from the settings page append `/kicad-doctor` entries to the log of the session they borrow (dsh logs every command).

## License

MIT

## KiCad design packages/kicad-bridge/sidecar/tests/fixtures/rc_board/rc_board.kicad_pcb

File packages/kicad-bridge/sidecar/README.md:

# dsh-kicad-sidecar

KiCad tools over MCP-style JSON-RPC on stdio. It backs the `ctx.kicad` service of
[dsh-kicad](../../../README.md) and also runs on its own as an MCP server.

- **Core is stdlib-only** (Python ≥ 3.10): a lossless S-expression reader/writer
  (untouched text round-trips byte for byte), a `.kicad_sch` model with atomic edit
  batches, symbol-library lookup/search, pin geometry, and a `kicad-cli` wrapper
  (ERC, DRC, netlist, BOM, SVG/PDF). For schematic → PCB sync: the board-side netlist
  (`netlist.py`) and KiCad's library-table chain (`lib_tables.py`); see
  [docs/pcb-architecture.md](../../../docs/pcb-architecture.md).
- **Extras:** `png` (cairosvg rasterizer; otherwise rsvg-convert/ImageMagick/Inkscape),
  `ipc` (kicad-python, for `ipc_status`), `dev` (pytest).

```sh
python -m dsh_kicad_sidecar [--kicad-cli PATH] [--root DIR ...]         # serve MCP on stdio
python -m dsh_kicad_sidecar --call read_schematic --args '{"path":"a.kicad_sch"}'
uvx --from . dsh-kicad-sidecar --root /path/to/project                   # same, through uv
```

Tools: `environment`, `doctor` (environment check with fixes and install commands), `read_schematic`, `list_components`, `get_symbol_pins`,
`list_nets`, `search_symbols`, `erc`, `drc`, `render`, `export_netlist`, `export_bom`,
`create_schematic`, `edit_schematic`, `ipc_status`. Each returns its value as
`structuredContent` plus a JSON text block; domain failures are `isError` results.

Tests: `uv run --extra dev pytest -q` (KiCad-dependent tests skip when `kicad-cli`
or the symbol libraries are missing). `tests/make_fixtures.py` regenerates the
fixtures with the editor itself.

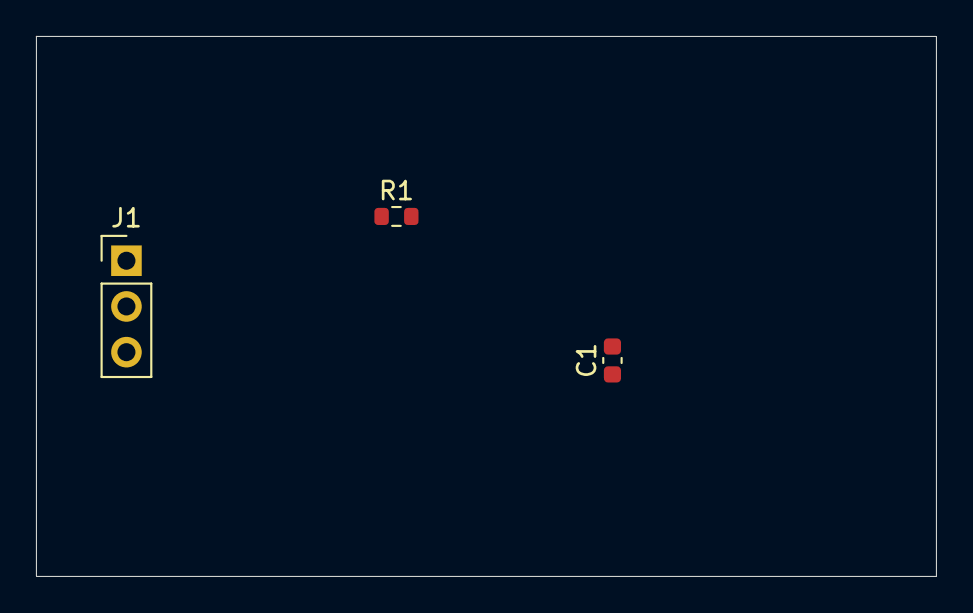
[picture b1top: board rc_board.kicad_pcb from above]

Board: 2 copper layers, 50.0 x 30.0 mm, 3 parts (0 on the bottom side), 3 nets, no tracks yet.

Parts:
C1: 100n; C_0603_1608Metric
J1: IN_OUT_GND; PinHeader_1x03_P2.54mm_Vertical
R1: 10k; R_0603_1608Metric

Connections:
GND: C1.2, J1.3
IN: J1.1, R1.1
OUT: C1.1, J1.2, R1.2
